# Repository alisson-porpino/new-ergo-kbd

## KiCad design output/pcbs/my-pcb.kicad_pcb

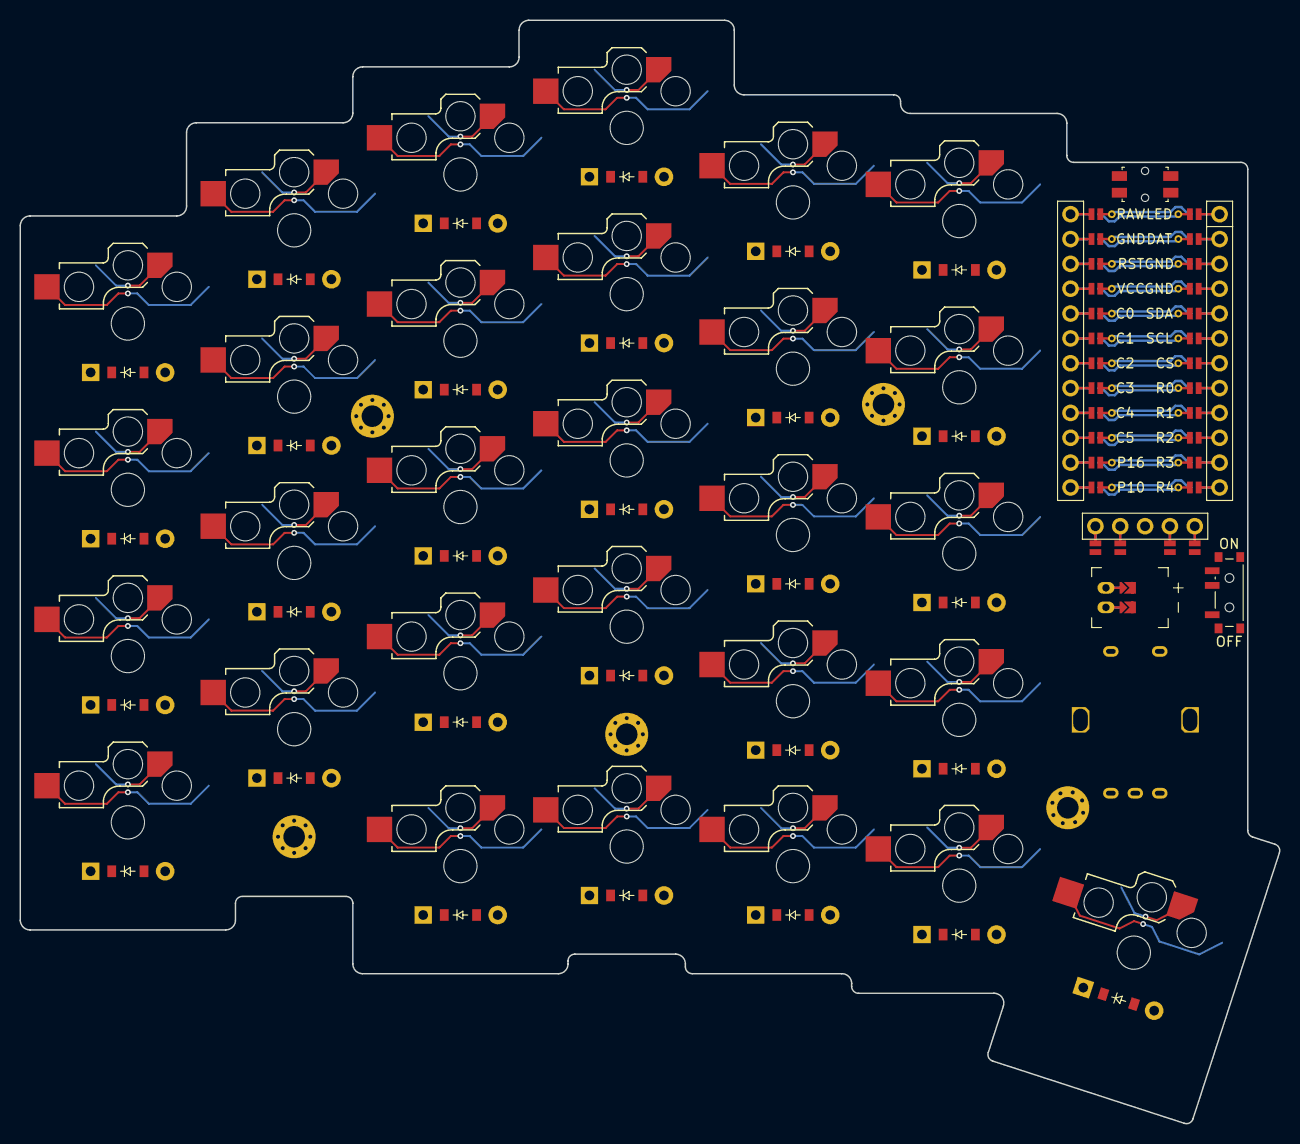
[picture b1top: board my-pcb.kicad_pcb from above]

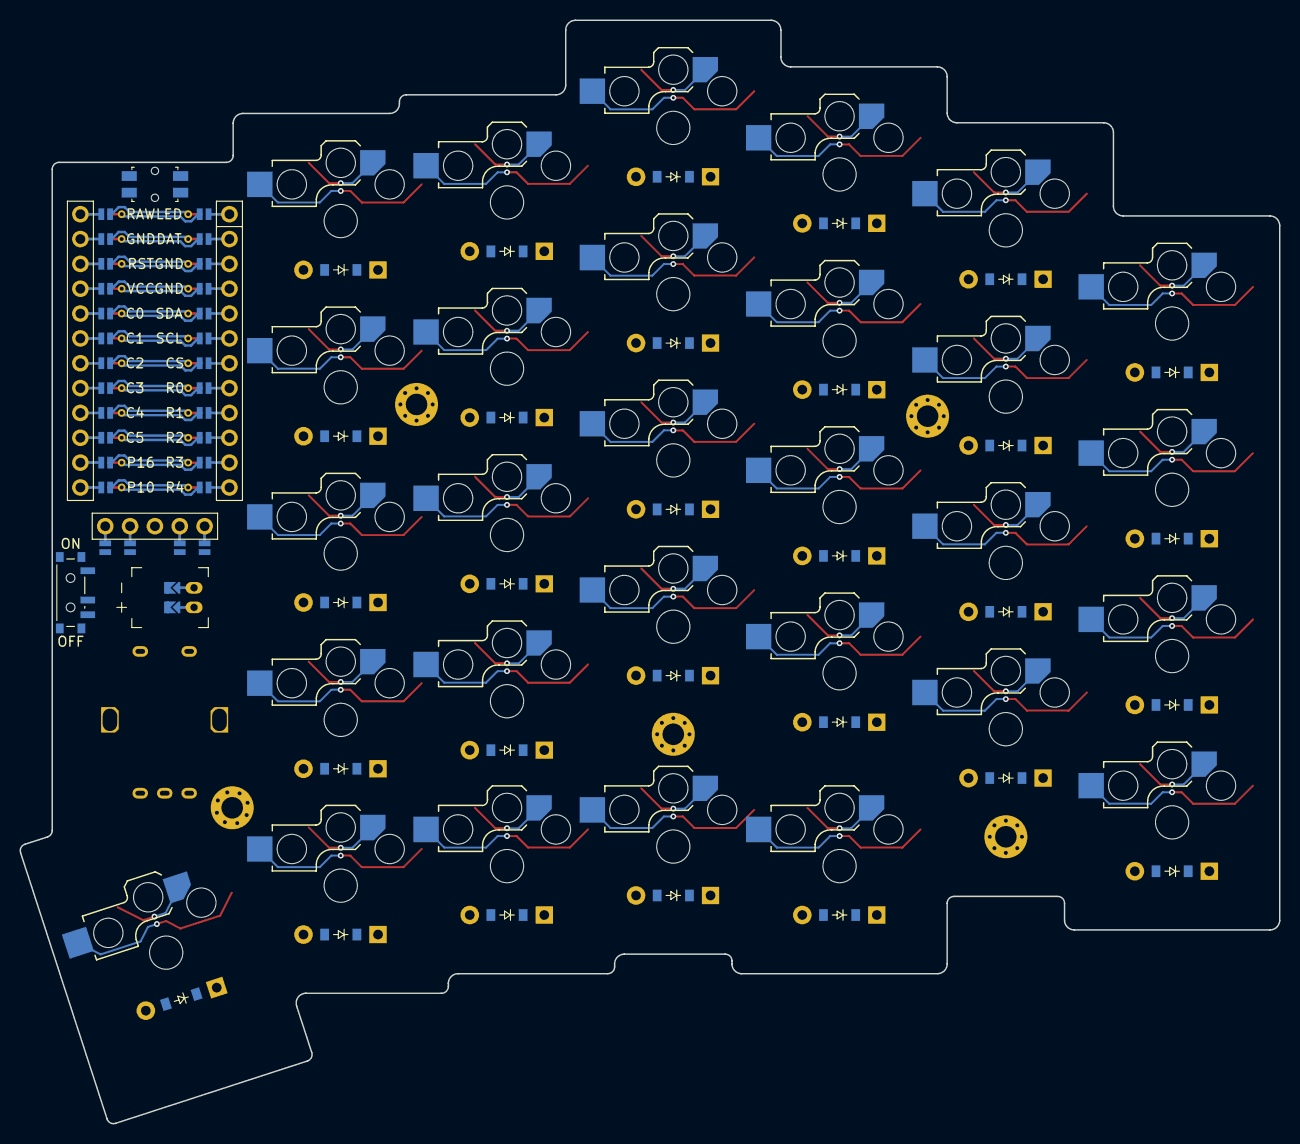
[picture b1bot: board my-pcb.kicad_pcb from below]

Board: 2 copper layers, 128.8 x 112.8 mm, 69 parts (29 on the bottom side), 25 nets.

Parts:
D1, D2, D3, D4, D5, D6, D7, D8, D9, D10, D11, D12, D13, D14, D15, D16, D17, D18, D19, D20, D21, D22, D23, D24, D25, D26, D27, D28, D29: ComboDiode
DISP1: display_nice_view
JST1: battery_connector_jst_ph_2
MCU1: mcu_nice_nano
PWR1: power_switch_smd_side
RE1: rotary_encoder_ec11_ec12
RST1: reset_switch_smd_side
S1, S2, S3, S4, S5, S6, S7, S8, S9, S10, S11, S12, S13, S14, S15, S16, S17, S18, S19, S20, S21, S22, S23, S24, S25, S26, S27, S28, S29: switch_choc_v1_v2
_1, _2, _3, _4, _5: MountingHole_2.2mm_M2_Pad_Via

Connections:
BAT_P: JST1.1, PWR1.2
C0: D1.1, D2.1, D3.1, D4.1, MCU1.120, S1.1, S2.1, S3.1, S4.1
C1: D5.1, D6.1, D7.1, D8.1, D25.1, MCU1.119, S5.1, S6.1, S7.1, S8.1, S25.1
C2: D9.1, D10.1, D11.1, D12.1, D26.1, MCU1.118, S9.1, S10.1, S11.1, S12.1, S26.1
C3: D13.1, D14.1, D15.1, D16.1, D27.1, MCU1.117, S13.1, S14.1, S15.1, S16.1, S27.1
C4: D17.1, D18.1, D19.1, D20.1, D28.1, MCU1.116, S17.1, S18.1, S19.1, S20.1, S28.1
C5: D21.1, D22.1, D23.1, D24.1, D29.1, MCU1.115, S21.1, S22.1, S23.1, S24.1, S29.1
CS: DISP1.10, DISP1.20, MCU1.107
DISP1_1: DISP1.1, DISP1.14, DISP1.27
DISP1_2: DISP1.2, DISP1.15, DISP1.26
DISP1_4: DISP1.4, DISP1.16, DISP1.25
DISP1_5: DISP1.5, DISP1.17, DISP1.24
GND: DISP1.11, DISP1.21, JST1.2, MCU1.103, MCU1.104, MCU1.123, RE1.B, RST1.1, RST1.3
JST1_1: JST1.11, JST1.21, JST1.31
JST1_2: JST1.12, JST1.22, JST1.32
R0: D4.2, D8.2, D12.2, D16.2, D20.2, D24.2, MCU1.108, S4.2, S8.2, S12.2, S16.2, S20.2, S24.2
R1: D3.2, D7.2, D11.2, D15.2, D19.2, D23.2, MCU1.109, S3.2, S7.2, S11.2, S15.2, S19.2, S23.2
R2: D2.2, D6.2, D10.2, D14.2, D18.2, D22.2, MCU1.110, S2.2, S6.2, S10.2, S14.2, S18.2, S22.2
R3: D1.2, D5.2, D9.2, D13.2, D17.2, D21.2, MCU1.111, S1.2, S5.2, S9.2, S13.2, S17.2, S21.2
R4: D25.2, D26.2, D27.2, D28.2, D29.2, MCU1.112, S25.2, S26.2, S27.2, S28.2, S29.2
RAW: MCU1.124, PWR1.1, PWR1.3
RST: MCU1.122, RST1.2, RST1.4
SCL: DISP1.12, DISP1.22, MCU1.106
SDA: DISP1.13, DISP1.23, MCU1.105
VCC: DISP1.3, MCU1.121

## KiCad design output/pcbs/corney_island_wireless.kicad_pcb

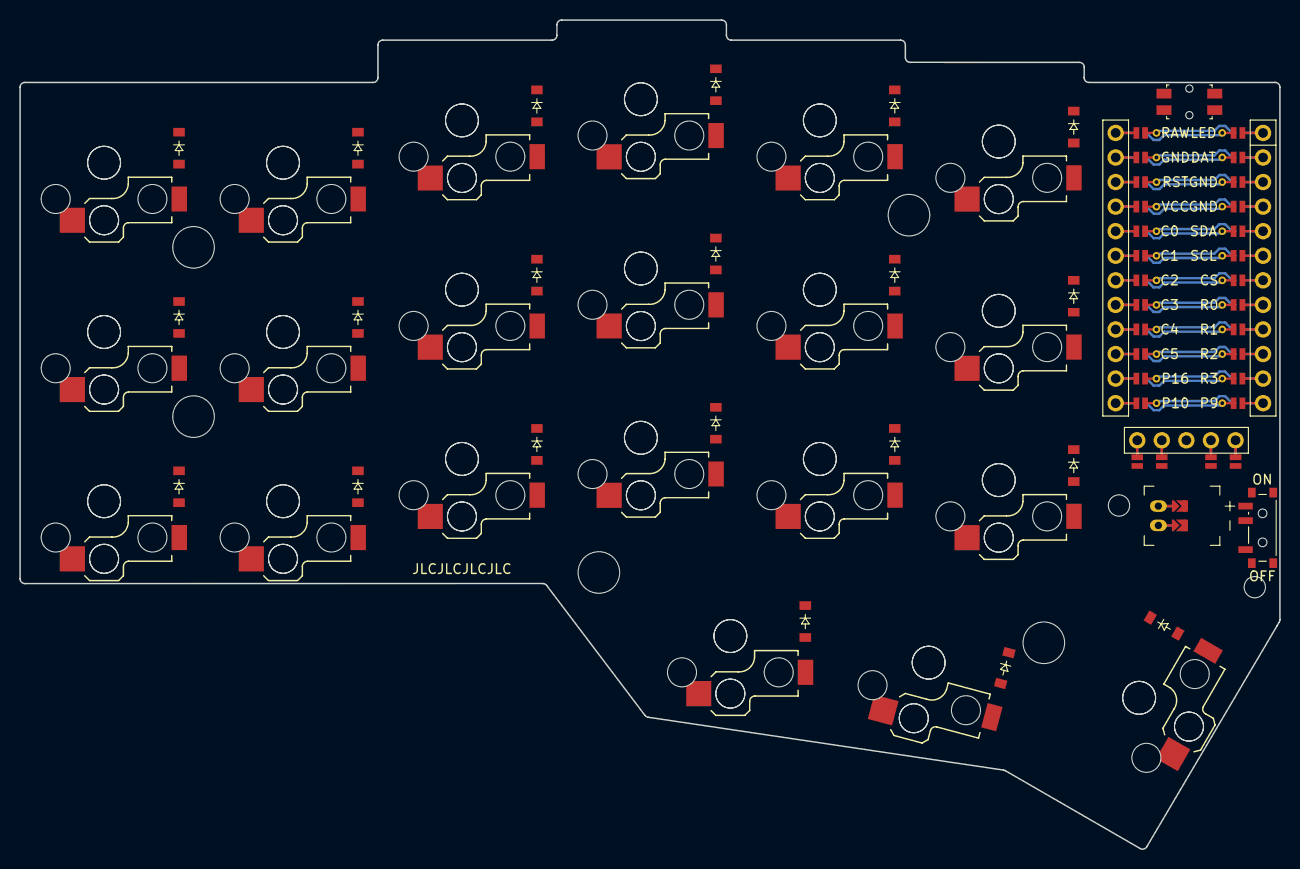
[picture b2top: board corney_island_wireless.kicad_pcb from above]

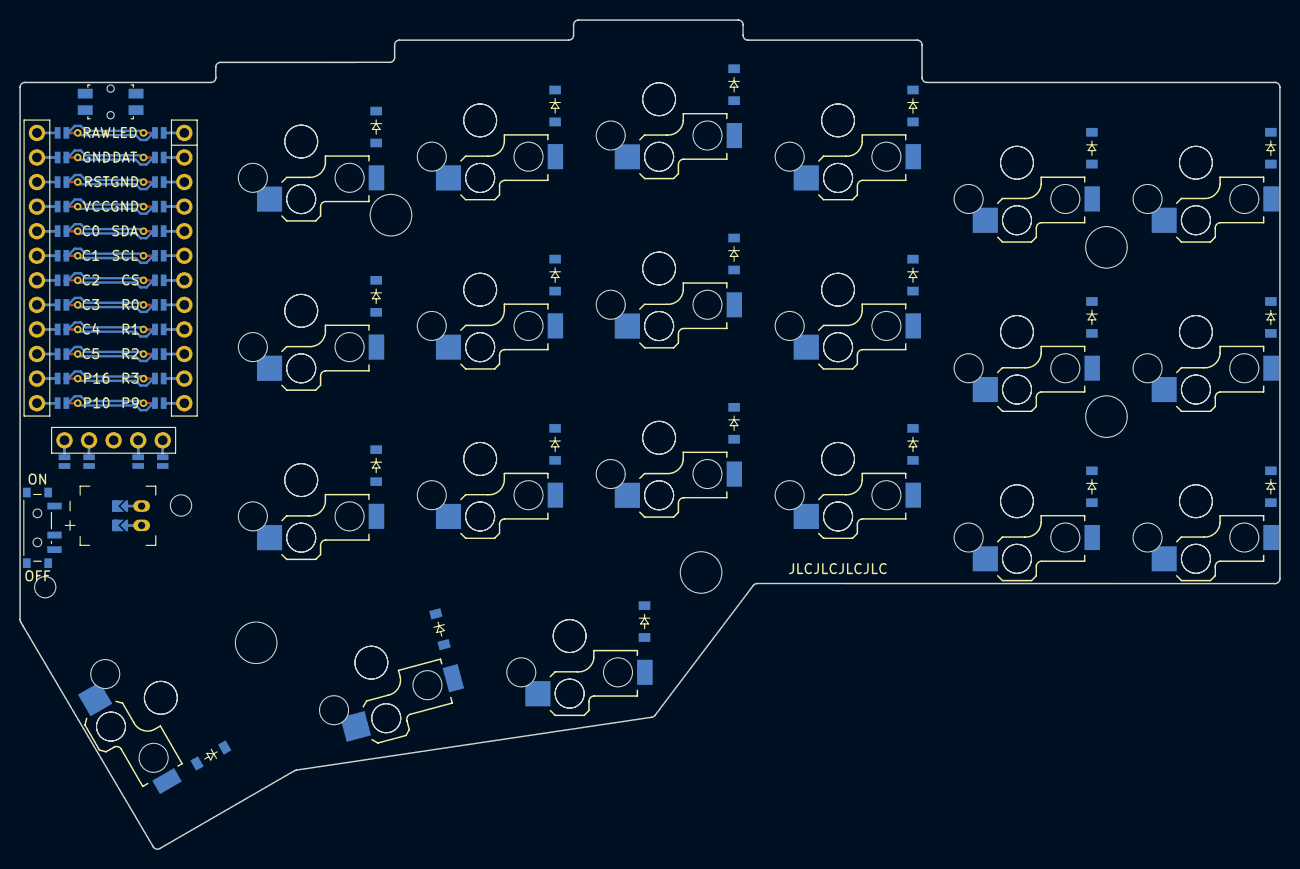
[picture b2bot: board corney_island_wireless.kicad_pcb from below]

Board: 2 copper layers, 130.3 x 85.7 mm, 96 parts (42 on the bottom side), 66 nets.

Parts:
D1, D2, D3, D4, D5, D6, D7, D8, D9, D10, D11, D12, D13, D14, D15, D16, D17, D18, D19, D20, D21, D22, D23, D24, D25, D26, D27, D28, D29, D30, D31, D32, D33, D34, D35, D36, D37, D38, D39, D40, D41, D42: diode_tht_sod123
DISP1: display_nice_view
JST1: battery_connector_jst_ph_2
MCU1: mcu_nice_nano
MH1, MH2, MH3, MH4, MH5, MH6, MH7: mounting_hole_npth
PWR1: power_switch_smd_side
RST1: reset_switch_smd_side
S1, S2, S3, S4, S5, S6, S7, S8, S9, S10, S11, S12, S13, S14, S15, S16, S17, S18, S19, S20, S21, S22, S23, S24, S25, S26, S27, S28, S29, S30, S31, S32, S33, S34, S35, S36, S37, S38, S39, S40, S41, S42: switch_choc_v1_v2

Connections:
BAT_P: JST1.1, PWR1.1, PWR1.3
C0: MCU1.120, S1.1, S2.1, S3.1, S22.1, S23.1, S24.1
C1: MCU1.119, S4.1, S5.1, S6.1, S25.1, S26.1, S27.1
C2: MCU1.118, S7.1, S8.1, S9.1, S28.1, S29.1, S30.1
C3: MCU1.117, S10.1, S11.1, S12.1, S19.1, S31.1, S32.1, S33.1, S40.1
C4: MCU1.116, S13.1, S14.1, S15.1, S20.1, S34.1, S35.1, S36.1, S41.1
C5: MCU1.115, S16.1, S17.1, S18.1, S21.1, S37.1, S38.1, S39.1, S42.1
CS: DISP1.10, DISP1.20, MCU1.107
DISP1_1: DISP1.1, DISP1.14, DISP1.27
DISP1_2: DISP1.2, DISP1.15, DISP1.26
DISP1_4: DISP1.4, DISP1.16, DISP1.25
DISP1_5: DISP1.5, DISP1.17, DISP1.24
GND: DISP1.11, DISP1.21, JST1.2, MCU1.103, MCU1.104, MCU1.123, RST1.1, RST1.3
JST1_1: JST1.11, JST1.21, JST1.31
JST1_2: JST1.12, JST1.22, JST1.32
R0: D3.1, D6.1, D9.1, D12.1, D15.1, D18.1, D24.1, D27.1, D30.1, D33.1, D36.1, D39.1, MCU1.108
R1: D2.1, D5.1, D8.1, D11.1, D14.1, D17.1, D23.1, D26.1, D29.1, D32.1, D35.1, D38.1, MCU1.109
R2: D1.1, D4.1, D7.1, D10.1, D13.1, D16.1, D22.1, D25.1, D28.1, D31.1, D34.1, D37.1, MCU1.110
R3: D19.1, D20.1, D21.1, D40.1, D41.1, D42.1, MCU1.111
RAW: MCU1.124, PWR1.2
RST: MCU1.122, RST1.2, RST1.4
SCL: DISP1.12, DISP1.22, MCU1.106
SDA: DISP1.13, DISP1.23, MCU1.105
VCC: DISP1.3, MCU1.121
far_home_B: D21.2, S21.2
far_home_F: D42.2, S42.2
index_bottom_B: D13.2, S13.2
index_bottom_F: D34.2, S34.2
index_home_B: D14.2, S14.2
index_home_F: D35.2, S35.2
index_top_B: D15.2, S15.2
index_top_F: D36.2, S36.2
inner_bottom_B: D16.2, S16.2
inner_bottom_F: D37.2, S37.2
inner_home_B: D17.2, S17.2
inner_home_F: D38.2, S38.2
inner_top_B: D18.2, S18.2
inner_top_F: D39.2, S39.2
mid_home_B: D20.2, S20.2
mid_home_F: D41.2, S41.2
middle_bottom_B: D10.2, S10.2
middle_bottom_F: D31.2, S31.2
middle_home_B: D11.2, S11.2
middle_home_F: D32.2, S32.2
middle_top_B: D12.2, S12.2
middle_top_F: D33.2, S33.2
near_home_B: D19.2, S19.2
near_home_F: D40.2, S40.2
outer_bottom_B: D1.2, S1.2
outer_bottom_F: D22.2, S22.2
outer_home_B: D2.2, S2.2
outer_home_F: D23.2, S23.2
outer_top_B: D3.2, S3.2
outer_top_F: D24.2, S24.2
pinky_bottom_B: D4.2, S4.2
pinky_bottom_F: D25.2, S25.2
pinky_home_B: D5.2, S5.2
pinky_home_F: D26.2, S26.2
pinky_top_B: D6.2, S6.2
pinky_top_F: D27.2, S27.2
ring_bottom_B: D7.2, S7.2
ring_bottom_F: D28.2, S28.2
ring_home_B: D8.2, S8.2
ring_home_F: D29.2, S29.2
ring_top_B: D9.2, S9.2
ring_top_F: D30.2, S30.2

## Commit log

2025-03-06 Testing repository
2025-03-15 cleanup
